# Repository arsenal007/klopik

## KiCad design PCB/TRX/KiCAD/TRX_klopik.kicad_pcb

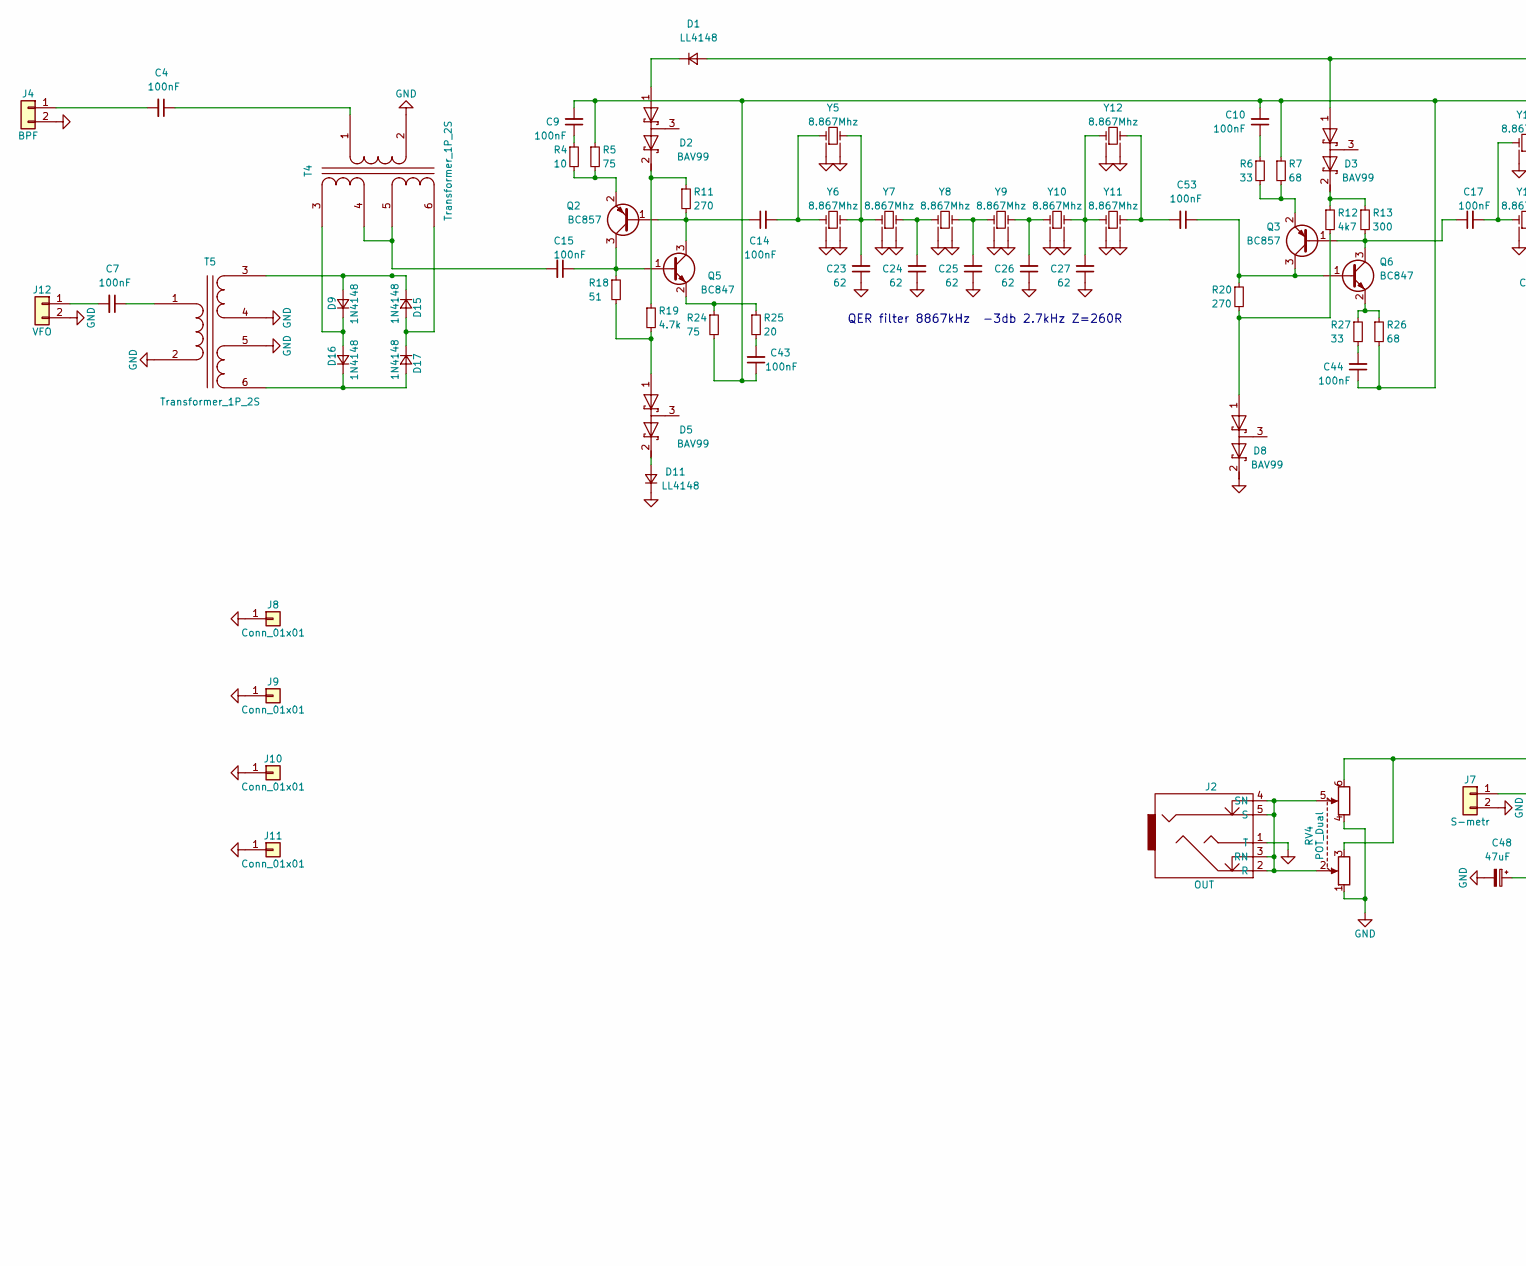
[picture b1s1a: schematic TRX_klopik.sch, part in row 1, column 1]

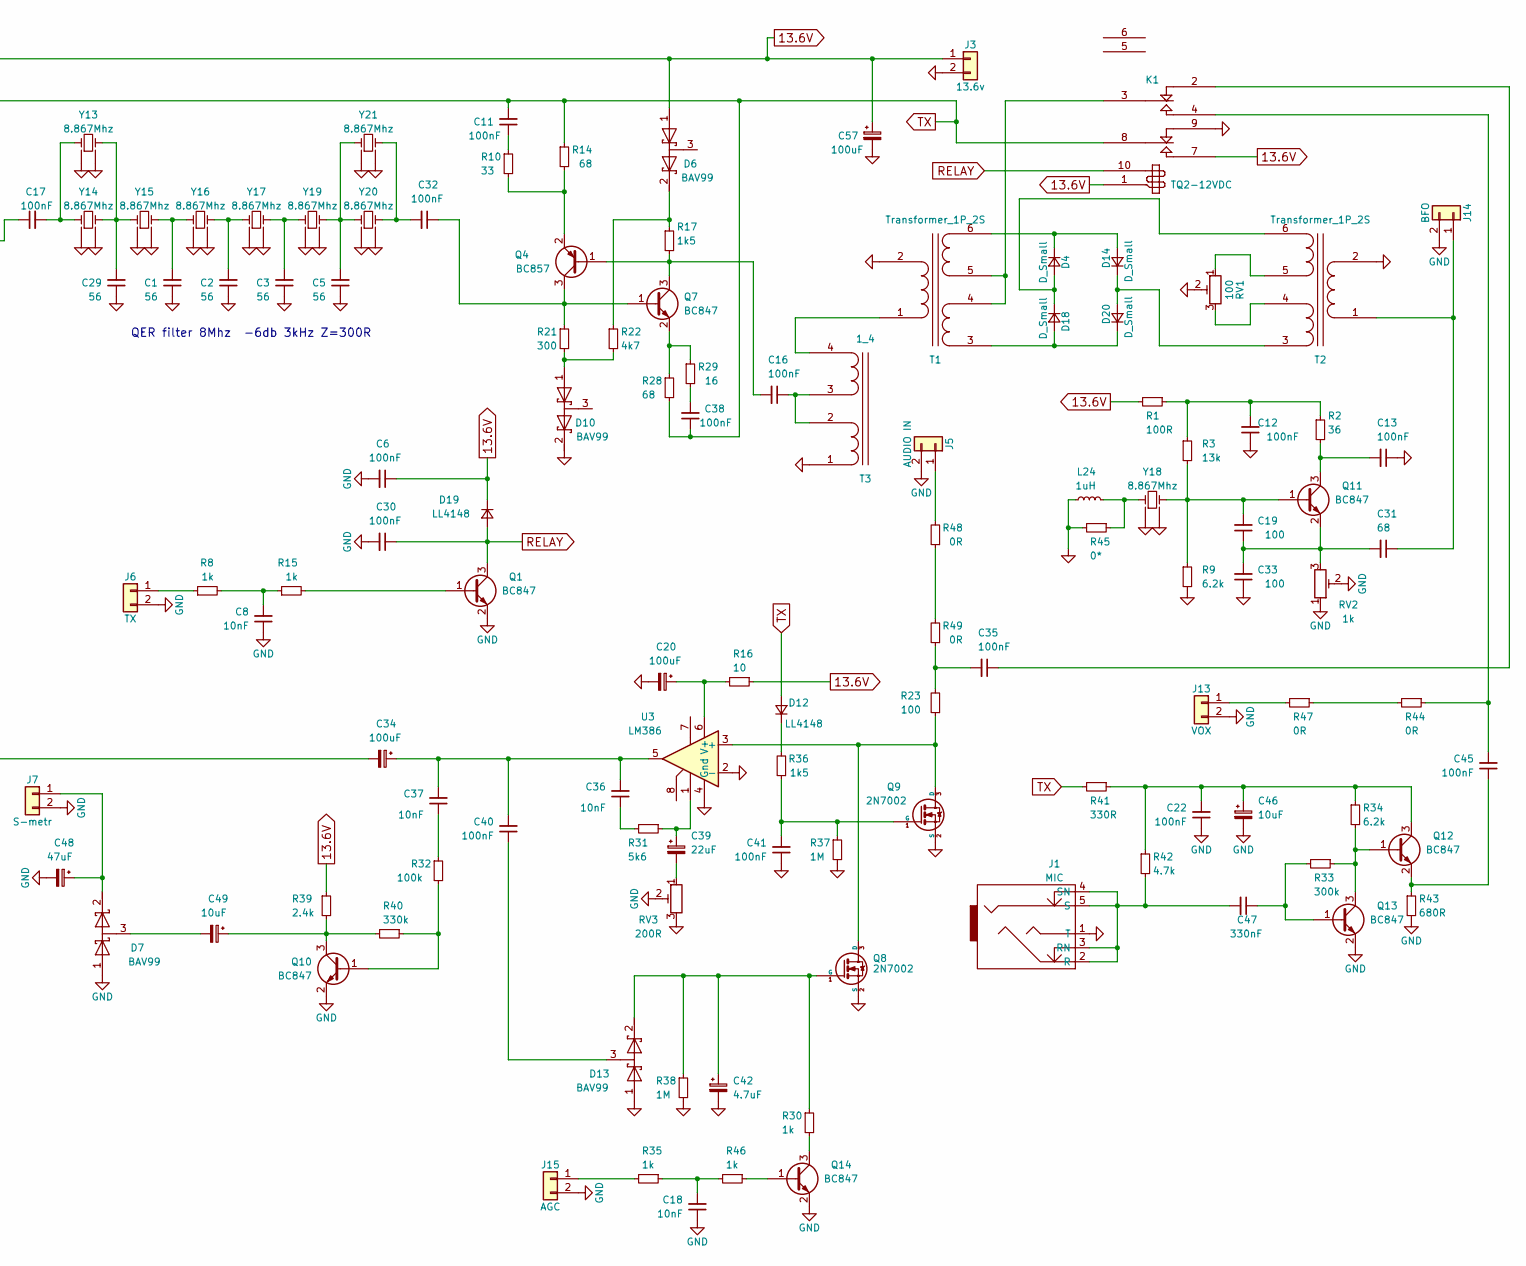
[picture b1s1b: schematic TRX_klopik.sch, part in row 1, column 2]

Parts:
C1, C2, C3, C5, C29: 56; C_1206_0603
C4, C6, C7, C9, C10, C11, C12, C13, C14, C15, C16, C17, C22, C30, C32, C35, C38, C40, C41, C43, C44, C45, C53: 100nF; C_1206_0603
C8, C18, C37: 10nF; C_0603_HandSoldering
C19, C33: 100; C_1206_0603
C20, C34, C57: 100uF; CP_Radial_D6.3mm_P2.50mm
C23, C24, C25, C26, C27: 62; C_1206_0603
C31: 68; C_1206_0603
C36: 10nF; C_1206_0603
C39: 22uF; CP_Tantalum_Case-A_EIA-3216-18_Hand
C42: 4.7uF; CP_Tantalum_Case-A_EIA-3216-18_Hand
C46, C49: 10uF; CP_Tantalum_Case-A_EIA-3216-18_Hand
C47: 330nF; C_1206_0603
C48: 47uF; CP_Radial_D6.3mm_P2.50mm
D1, D11, D12, D19: LL4148; D_MiniMELF_Handsoldering
D2, D3, D5, D6, D7, D8, D10, D13: BAV99; SOT-23_Handsoldering
D4, D14, D18, D20: D_Small; D_DO-35_SOD27_P7.62mm_Horizontal
D9, D15, D16, D17: 1N4148; D_DO-35_SOD27_P7.62mm_Horizontal
J1: MIC; audio_jack_3_5mm_PJ307
J2: OUT; audio_jack_3_5mm_PJ307
J3: 13.6v; Pin_Header_Straight_1x02_Pitch2.54mm
J4: BPF; RFCONNECTOR
J5: AUDIO IN; Pin_Header_Straight_1x02_Pitch2.54mm
J6: TX; Pin_Header_Straight_1x02_Pitch2.54mm
J7: S-metr; Pin_Header_Straight_1x02_Pitch2.54mm
J8, J9, J10, J11: Conn_01x01; MountingHole_3.2mm_M3_DIN965_Pad
J12: VFO; RFCONNECTOR
J13: VOX; Pin_Header_Straight_1x02_Pitch2.54mm
J14: BFO; Pin_Header_Straight_1x02_Pitch2.54mm
J15: AGC; Pin_Header_Straight_1x02_Pitch2.54mm
K1: TQ2-12VDC; Relay_DPDT_FRT5
L24: 1uH; Choke_Toroid_6,5x13mm_Vertical
Q1, Q5, Q6, Q7, Q10, Q11, Q12, Q13, Q14: BC847; SOT-23_Handsoldering
Q2, Q3, Q4: BC857; SOT-23_Handsoldering
Q8, Q9: 2N7002; SOT-23_Handsoldering
R1: 100R; R_1206_0603
R2: 36; R_1206_0603
R3: 13k; R_1206_0603
R4, R16: 10; R_1206_0603
R5, R24: 75; R_1206_0603
R6, R10, R27: 33; R_1206_0603
R7, R14, R26, R28: 68; R_1206_0603
R8, R15, R30, R35, R46: 1k; R_1206_0603
R9, R34: 6.2k; R_1206_0603
R11, R20: 270; R_1206_0603
R12, R22: 4k7; R_0603_HandSoldering
R13, R21: 300; R_1206_0603
R17: 1k5; R_1206_0603
R18: 51; R_1206_0603
R19: 4.7k; R_0603_HandSoldering
R23: 100; R_1206_0603
R25: 20; R_1206_0603
R29: 16; R_1206_0603
R31: 5k6; R_1206_0603
R32: 100k; R_1206_0603
R33: 300k; R_1206_0603
R36: 1k5; R_0805_HandSoldering
R37, R38: 1M; R_1206_0603
R39: 2.4k; R_1206_0603
R40: 330k; R_1206_0603
R41: 330R; R_1206_0603
R42: 4.7k; R_1206_0603
R43: 680R; R_1206_0603
R44, R47, R48, R49: 0R; R_1206_0603
R45: 0*; R_1206_0603
RV1: 100; Potentiometer_Trimmer_Piher_PT-6v_Horizontal
RV2: 1k; Potentiometer_Trimmer_Piher_PT-6v_Horizontal
RV3: 200R; Potentiometer_Trimmer_Piher_PT-6v_Horizontal
RV4: POT_Dual; Potentiometer_WH148_Double
T1, T2, T4, T5: Transformer_1P_2S; HF_transf3
T3: 1_4; TF14
U3: LM386; SOIC-8_3.9x4.9mm_Pitch1.27mm
Y5, Y6, Y7, Y8, Y9, Y10, Y11, Y12, Y13, Y14, Y15, Y16, Y17, Y18, Y19, Y20, Y21: 8.867Mhz; Crystal_HC49-U_Vertical

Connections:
13.6V: C6.1, C57.1, D1.2 (A), D3.1 (A), D6.1 (A), D19.1 (K), J3.1, K1.1 (+), K1.7 (T1), R1.2, R16.1, R39.1
GND: C1.1, C2.1, C3.1, C5.1, C6.2, C8.1, C12.1, C13.1, C18.1, C20.2, C22.1, C23.1, C24.1, C25.1, C26.1, C27.1, C29.1, C30.2, C33.1, C41.1, C42.2, C46.2, C48.2, C57.2, D7.1 (A), D8.2 (K), D10.2 (K), D11.1 (K), D13.1 (A), J1.1 (T), J2.1 (T), J3.2, J4.2, J5.2, J6.2, J7.2, J8.1, J9.1, J10.1, J11.1, J12.2, J13.2, J14.2, J15.2, K1.9 (R1), L24.1, Q1.2 (E), Q8.2 (S), Q9.2 (S), Q10.2 (E), Q13.2 (E), Q14.2 (E), R9.2, R37.2, R38.2, R43.2, R45.2, RV1.2, RV2.1, RV2.2, RV3.2, RV3.3, RV4.1, RV4.4, T1.2 (AB), T2.2 (AB), T3.1 (SA), T4.2 (AB), T5.2 (AB), T5.4 (SB), T5.5 (SC), U3.2 (-), U3.4 (Gnd), Y5.3 (GND), Y5.4 (GND), Y6.3 (GND), Y6.4 (GND), Y7.3 (GND), Y7.4 (GND), Y8.3 (GND), Y8.4 (GND), Y9.3 (GND), Y9.4 (GND), Y10.3 (GND), Y10.4 (GND), Y11.3 (GND), Y11.4 (GND), Y12.3 (GND), Y12.4 (GND), Y13.3 (GND), Y13.4 (GND), Y14.3 (GND), Y14.4 (GND), Y15.3 (GND), Y15.4 (GND), Y16.3 (GND), Y16.4 (GND), Y17.3 (GND), Y17.4 (GND), Y18.3 (GND), Y18.4 (GND), Y19.3 (GND), Y19.4 (GND), Y20.3 (GND), Y20.4 (GND), Y21.3 (GND), Y21.4 (GND)
unnamed: C1.2, Y15.2, Y16.1
unnamed: C2.2, Y16.2, Y17.1
unnamed: C3.2, Y17.2, Y19.1
unnamed: C4.1, T4.1 (AA)
unnamed: C4.2, J4.1
unnamed: C5.2, Y19.2, Y20.1, Y21.1
unnamed: C7.1, T5.1 (AA)
unnamed: C7.2, J12.1
unnamed: C8.2, R8.2, R15.1
unnamed: C9.1, R4.1
unnamed: C10.1, R6.1
unnamed: C11.1, R10.1
unnamed: C12.2, R1.1, R2.1, R3.1
unnamed: C13.2, Q11.3 (C), R2.2
unnamed: C14.1, Q2.1 (B), Q5.3 (C), R11.2
unnamed: C14.2, Y5.1, Y6.1
unnamed: C15.1, Q2.3 (C), Q5.1 (B), R18.1
unnamed: C15.2, T4.4 (SB), T4.5 (SC)
unnamed: C16.1, T3.2 (SB), T3.3 (SC)
unnamed: C16.2, Q4.1 (B), Q7.3 (C), R17.2
unnamed: C17.1, Q3.1 (B), Q6.3 (C), R13.2
unnamed: C17.2, Y13.1, Y14.1
unnamed: C18.2, R35.1, R46.2
unnamed: C19.1, C31.2, C33.2, Q11.2 (E), RV2.3
unnamed: C19.2, Q11.1 (B), R3.2, R9.1, Y18.2
unnamed: C20.1, R16.2, U3.6 (V+)
unnamed: C22.2, C46.1, Q12.3 (C), R34.1, R41.1, R42.1
unnamed: C23.2, Y5.2, Y6.2, Y7.1
unnamed: C24.2, Y7.2, Y8.1
unnamed: C25.2, Y8.2, Y9.1
unnamed: C26.2, Y9.2, Y10.1
unnamed: C27.2, Y10.2, Y11.1, Y12.1
unnamed: C29.2, Y13.2, Y14.2, Y15.1
unnamed: C31.1, J14.1, T2.1 (AA)
unnamed: C32.1, Q4.3 (C), Q7.1 (B), R21.1
unnamed: C32.2, Y20.2, Y21.2
unnamed: C34.1, C36.2, C37.2, C40.2, U3.5
unnamed: C34.2, RV4.3, RV4.6
unnamed: C35.1, K1.2 (R2)
unnamed: C35.2, R23.2, R49.1
unnamed: C36.1, R31.2
unnamed: C37.1, R32.1
unnamed: C38.2, R29.2
unnamed: C39.1, R31.1, U3.1
unnamed: C39.2, RV3.1
unnamed: C40.1, D13.3 (common)
unnamed: C41.2, Q9.1 (G), R36.1, R37.1
unnamed: C42.1, D13.2 (K), Q8.1 (G), R30.1, R38.1
unnamed: C43.2, R25.2
unnamed: C44.2, R27.2
unnamed: C45.1, Q12.2 (E), R43.1
unnamed: C45.2, K1.4 (T2), R44.1
unnamed: C47.1, Q13.1 (B), R33.2
unnamed: C47.2, J1.2 (R), J1.3 (RN), J1.4 (SN), J1.5 (S), R42.2
unnamed: C48.1, D7.2 (K), J7.1
unnamed: C49.1, Q10.3 (C), R39.2, R40.2
unnamed: C49.2, D7.3 (common)
unnamed: C53.1, Q3.3 (C), Q6.1 (B), R20.1
unnamed: C53.2, Y11.2, Y12.2
unnamed: D1.1 (K), D2.1 (A)
unnamed: D2.2 (K), R11.1, R19.1
unnamed: D3.2 (K), R12.1, R13.1
unnamed: D5.1 (A), R18.2, R19.2
unnamed: D6.2 (K), R17.1, R22.1
unnamed: D8.1 (A), R12.2, R20.2
unnamed: D10.1 (A), R21.2, R22.2
unnamed: D5.2 (K), D11.2 (A)
unnamed: D12.1 (K), R36.2
unnamed: D14.1 (K), D20.2 (A), T2.3 (SA)
unnamed: D4.1 (K), D14.2 (A), T1.6 (SD)
unnamed: D9.2 (A), D15.1 (K), T5.3 (SA)
unnamed: D15.2 (A), D17.1 (K), T4.6 (SD)
unnamed: D16.1 (K), D17.2 (A), T5.6 (SD)
unnamed: D9.1 (K), D16.2 (A), T4.3 (SA)
unnamed: D4.2 (A), D18.1 (K), T2.6 (SD)
unnamed: D18.2 (A), D20.1 (K), T1.3 (SA)
unnamed: J2.2 (R), J2.3 (RN), J2.4 (SN), J2.5 (S), RV4.2, RV4.5
unnamed: J5.1, R48.2
unnamed: J6.1, R8.1
unnamed: J13.1, R47.2
unnamed: J15.1, R35.2
unnamed: K1.3 (C2), T1.4 (SB), T1.5 (SC)
unnamed: L24.2, R45.1, Y18.1
unnamed: Q1.1 (B), R15.2
unnamed: Q2.2 (E), R4.2, R5.2
unnamed: Q3.2 (E), R6.2, R7.2
unnamed: Q4.2 (E), R10.2, R14.2
unnamed: Q5.2 (E), R24.1, R25.1
unnamed: Q6.2 (E), R26.1, R27.1
unnamed: Q7.2 (E), R28.1, R29.1
unnamed: Q8.3 (D), Q9.3 (D), R23.1, U3.3 (+)
unnamed: Q10.1 (B), R32.2, R40.1
unnamed: Q12.1 (B), Q13.3 (C), R33.1, R34.2
unnamed: Q14.1 (B), R46.1
unnamed: Q14.3 (C), R30.2
unnamed: R44.2, R47.1
unnamed: R48.1, R49.2
unnamed: RV1.1, T2.5 (SC)
unnamed: RV1.3, T2.4 (SB)
unnamed: T1.1 (AA), T3.4 (SD)
RELAY: C30.1, D19.2 (A), K1.10 (-), Q1.3 (C)
TX: C9.2, C10.2, C11.2, C38.1, C43.1, C44.1, D12.2 (A), K1.8 (C1), R5.1, R7.1, R14.1, R24.2, R26.2, R28.2, R41.2

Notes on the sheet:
QER filter 8867kHz -3db 2.7kHz Z=260R
QER filter 8Mhz -6db 3kHz Z=300R

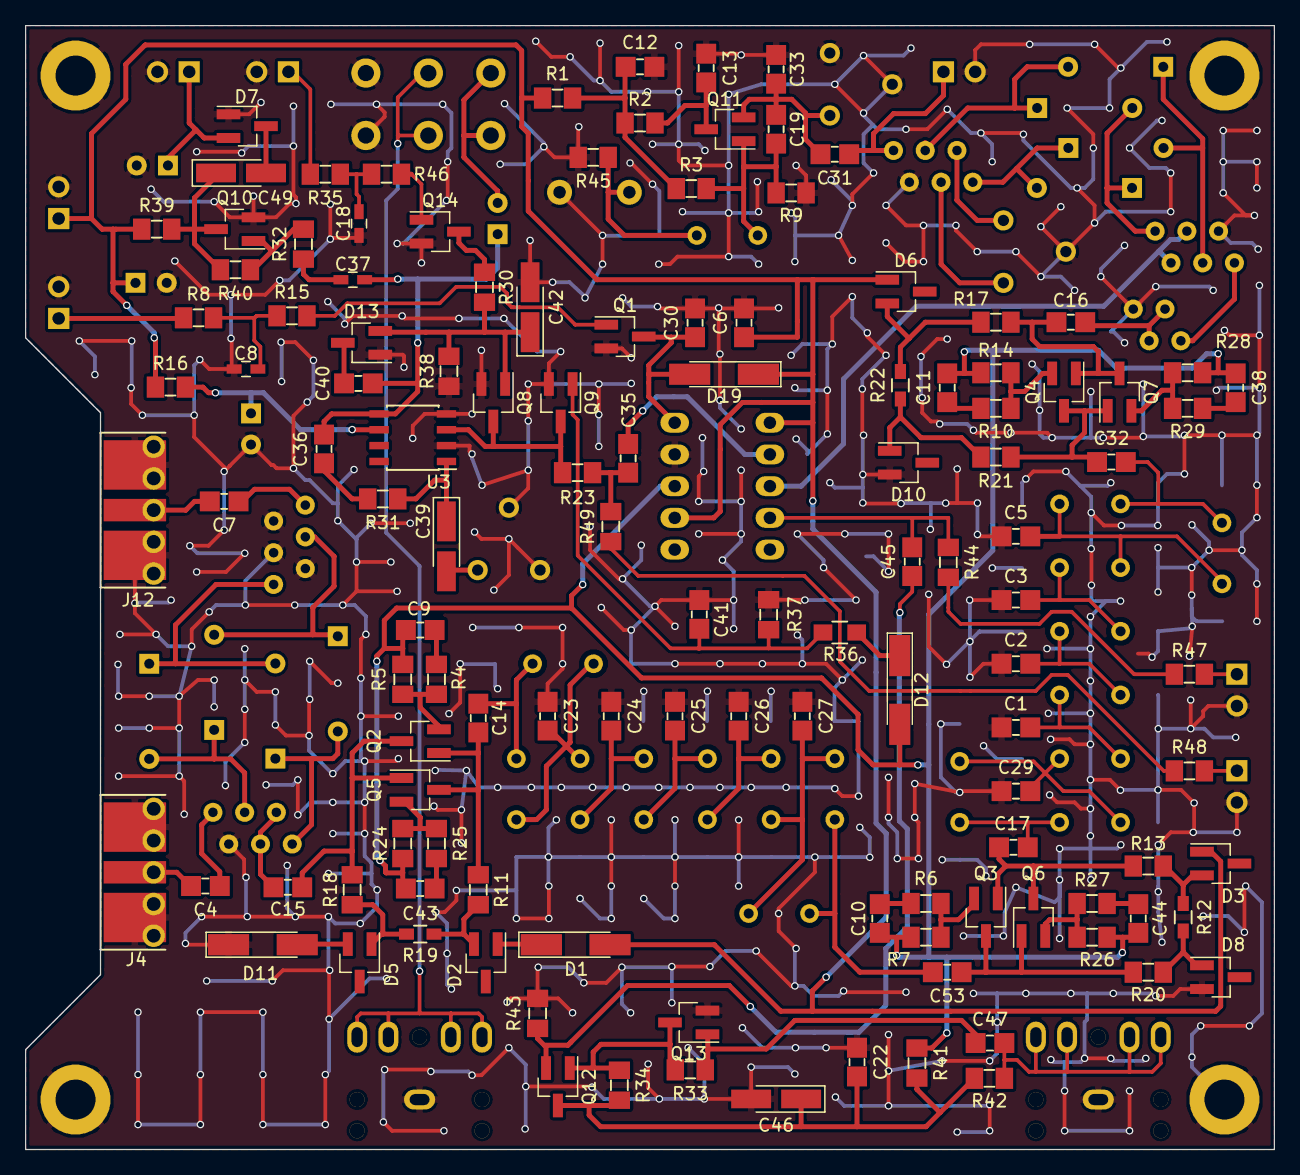
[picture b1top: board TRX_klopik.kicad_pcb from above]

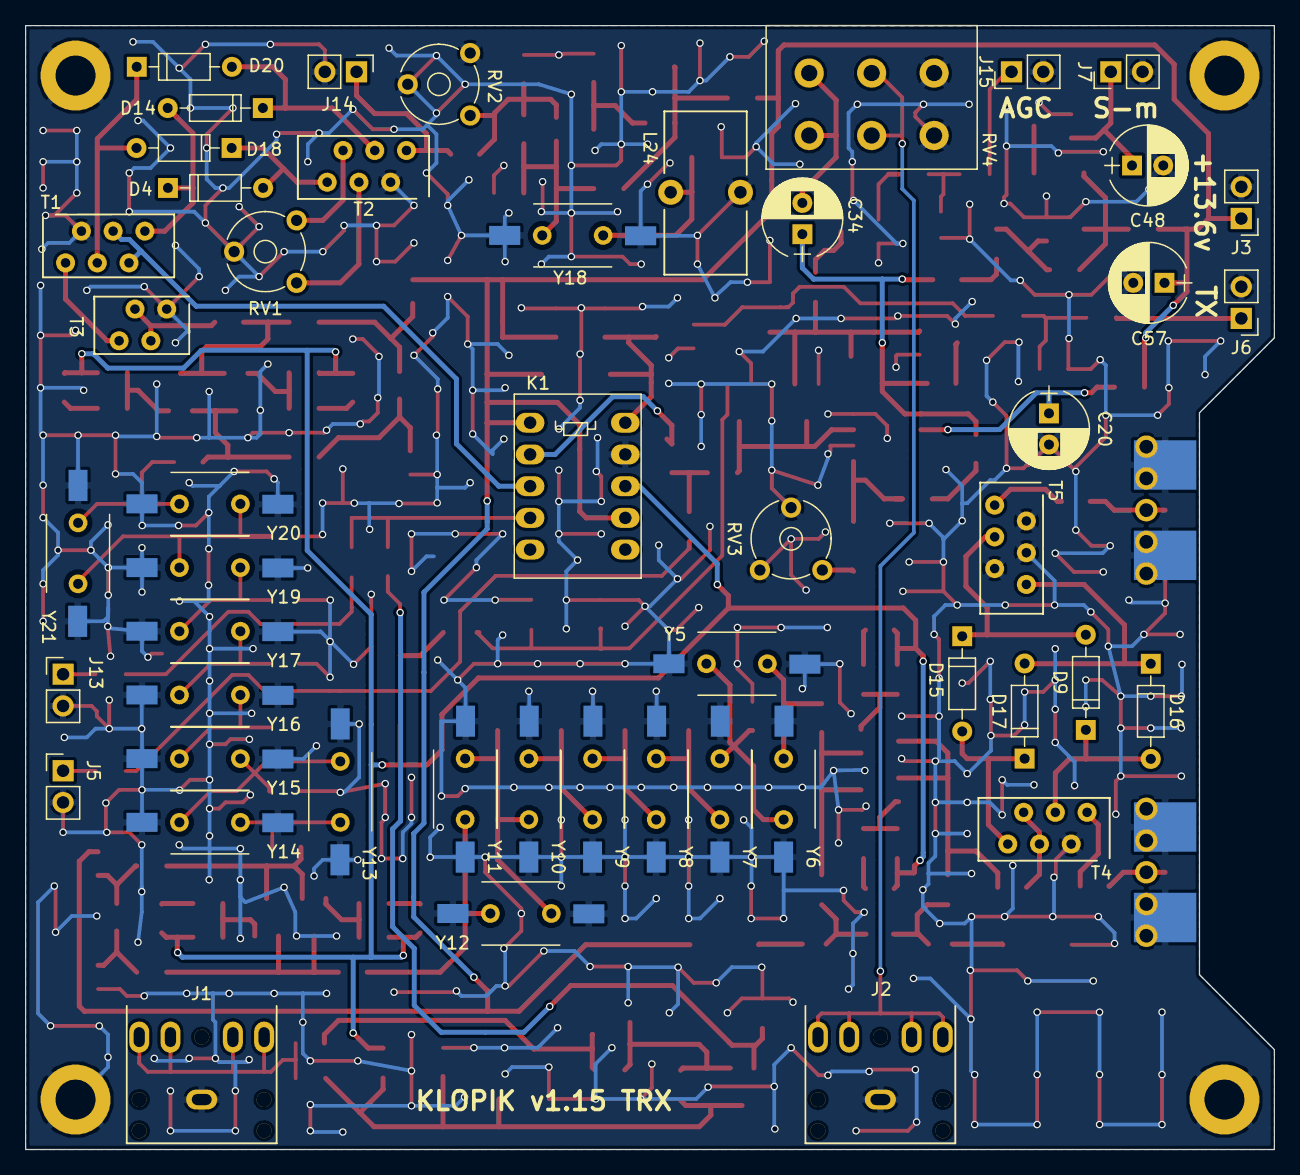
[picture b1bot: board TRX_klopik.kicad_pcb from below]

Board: 2 copper layers, 100.0 x 90.0 mm, 176 parts (51 on the bottom side), 104 nets.

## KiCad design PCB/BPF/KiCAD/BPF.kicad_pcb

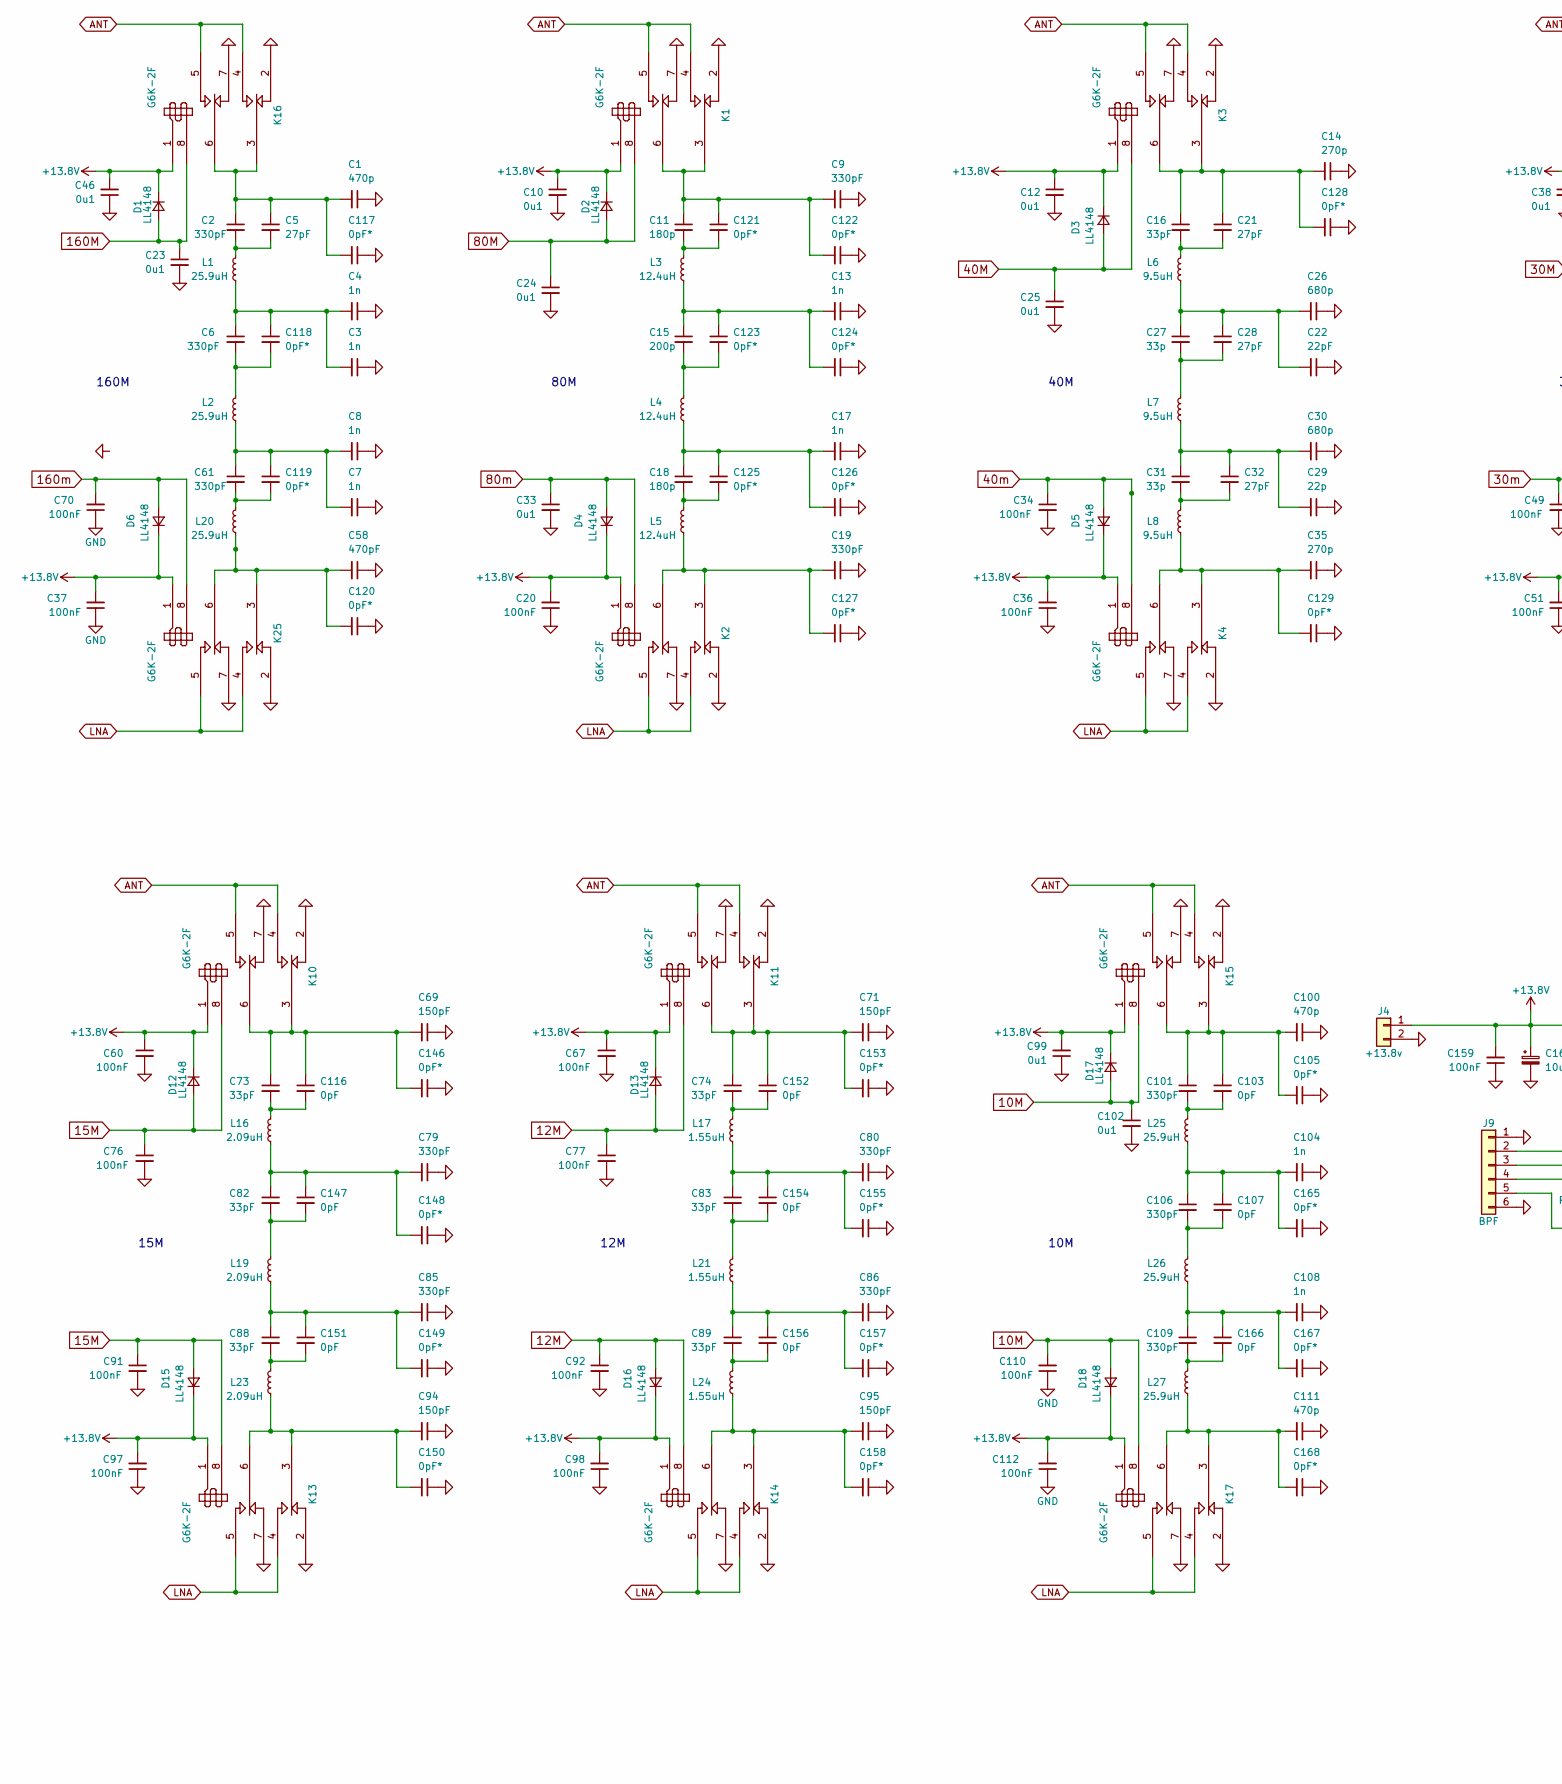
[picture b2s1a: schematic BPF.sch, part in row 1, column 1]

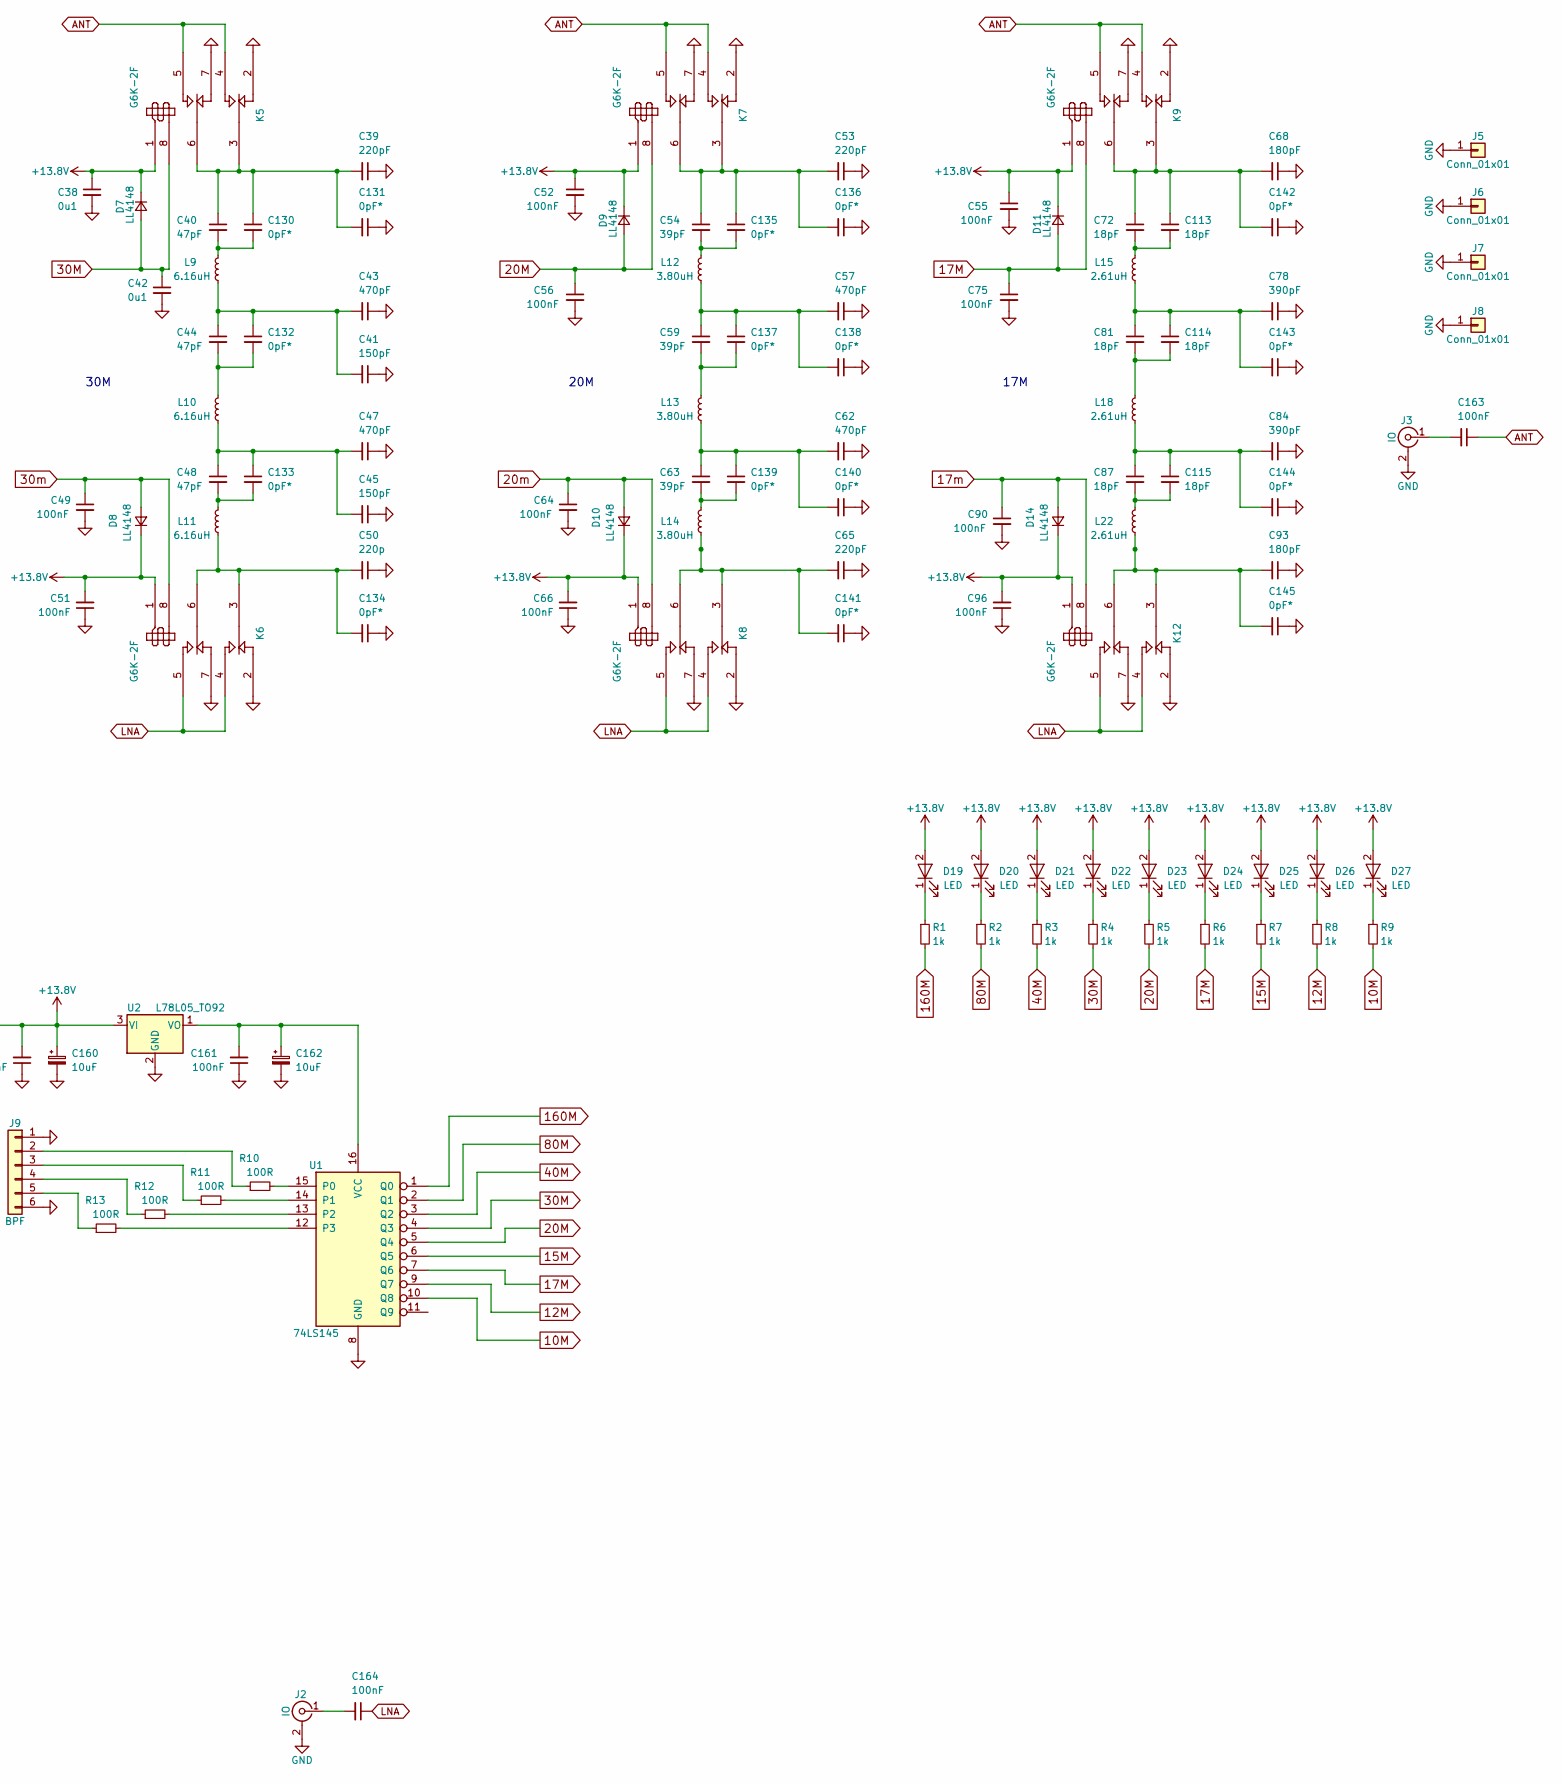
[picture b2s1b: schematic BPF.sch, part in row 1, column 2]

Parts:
C1, C100, C111: 470p; C_1206_0603
C2, C6, C9, C19, C61, C79, C80, C85, C86, C101, C106, C109: 330pF; C_1206_0603
C3, C4, C7, C8, C13, C17, C104, C108: 1n; C_1206_0603
C5, C21, C28, C32: 27pF; C_1206_0603
C10, C12, C23, C24, C25, C33, C38, C42, C46, C99, C102: 0u1; C_1206_0603
C11, C18: 180p; C_1206_0603
C14, C35: 270p; C_1206_0603
C15: 200p; C_1206_0603
C16, C73, C74, C82, C83, C88, C89: 33pF; C_1206_0603
C20, C34, C36, C37, C49, C51, C52, C55, C56, C60, C64, C66, C67, C70, C75, C76, C77, C90, C91, C92, C96, C97, C98, C110, C112, C159, C161, C163, C164: 100nF; C_1206_0603
C22: 22pF; C_1206_0603
C26, C30: 680p; C_1206_0603
C27, C31: 33p; C_1206_0603
C29: 22p; C_1206_0603
C39, C53, C65: 220pF; C_1206_0603
C40, C44, C48: 47pF; C_1206_0603
C41, C45, C69, C71, C94, C95: 150pF; C_1206_0603
C43, C47, C57, C58, C62: 470pF; C_1206_0603
C50: 220p; C_1206_0603
C54, C59, C63: 39pF; C_1206_0603
C68, C93: 180pF; C_1206_0603
C72, C81, C87, C113, C114, C115: 18pF; C_1206_0603
C78, C84: 390pF; C_1206_0603
C103, C107, C116, C147, C151, C152, C154, C156, C166: 0pF; C_1206_0603
C105, C117, C118, C119, C120, C121, C122, C123, C124, C125, C126, C127, C128, C129, C130, C131, C132, C133, C134, C135, C136, C137, C138, C139, C140, C141, C142, C143, C144, C145, C146, C148, C149, C150, C153, C155, C157, C158, C165, C167, C168: 0pF*; C_1206_0603
C160, C162: 10uF; CP_Tantalum_Case-A_EIA-3216-18_Hand
D1, D2, D3, D4, D5, D6, D7, D8, D9, D10, D11, D12, D13, D14, D15, D16, D17, D18: LL4148; D_MiniMELF_Handsoldering
D19, D20, D21, D22, D23, D24, D25, D26, D27: LED; LED_D3.0mm
J2, J3: IO; RFCONNECTOR
J4: +13.8v; Pin_Header_Straight_1x02_Pitch2.54mm
J5, J6, J7, J8: Conn_01x01; MountingHole_3.2mm_M3_DIN965_Pad
J9: BPF; Pin_Header_Straight_1x06_Pitch2.54mm
K1, K2, K3, K4, K5, K6, K7, K8, K9, K10, K11, K12, K13, K14, K15, K16, K17, K25: G6K-2F; Relay_G6K-2F
L1, L2, L20, L25, L26, L27: 25.9uH; Choke_Toroid_6,5x13mm_Vertical
L3, L4, L5: 12.4uH; Choke_Toroid_6,5x13mm_Vertical
L6, L7, L8: 9.5uH; Choke_Toroid_6,5x13mm_Vertical
L9, L10, L11: 6.16uH; Choke_Toroid_6,5x13mm_Vertical
L12, L13, L14: 3.80uH; Choke_Toroid_6,5x13mm_Vertical
L15, L18, L22: 2.61uH; Choke_Toroid_6,5x13mm_Vertical
L16, L19, L23: 2.09uH; Choke_Toroid_6,5x13mm_Vertical
L17, L21, L24: 1.55uH; Choke_Toroid_6,5x13mm_Vertical
R1, R2, R3, R4, R5, R6, R7, R8, R9: 1k; R_1206_0603
R10, R11, R12, R13: 100R; R_0603_HandSoldering
U1: 74LS145; SOIC-16_3.9x9.9mm_Pitch1.27mm
U2: L78L05_TO92; TO-92_Inline_Wide

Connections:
10M: C102.1, C110.2, D17.2 (A), D18.2 (A), K15.8 (-), K17.8 (-), R9.2, U1.10 (Q8)
12M: C77.1, C92.1, D13.2 (A), D16.2 (A), K11.8 (-), K14.8 (-), R8.2, U1.9 (Q7)
15M: C76.1, C91.1, D12.2 (A), D15.2 (A), K10.8 (-), K13.8 (-), R7.2, U1.6 (Q5)
17M: C75.1, C90.1, D11.2 (A), D14.2 (A), K9.8 (-), K12.8 (-), R6.2, U1.7 (Q6)
20M: C56.1, C64.1, D9.2 (A), D10.2 (A), K7.8 (-), K8.8 (-), R5.2, U1.5 (Q4)
30M: C42.1, C49.1, D7.2 (A), D8.2 (A), K5.8 (-), K6.8 (-), R4.2, U1.4 (Q3)
40M: C25.1, C34.1, D3.2 (A), D5.2 (A), K3.8 (-), K4.8 (-), R3.2, U1.3 (Q2)
80M: C24.1, C33.1, D2.2 (A), D4.2 (A), K1.8 (-), K2.8 (-), R2.2, U1.2 (Q1)
160M: C23.1, C70.2, D1.2 (A), D6.2 (A), K16.8 (-), K25.8 (-), R1.2, U1.1 (Q0)
+13.8V: C10.1, C12.1, C20.2, C36.2, C37.2, C38.1, C46.2, C51.2, C52.1, C55.1, C60.1, C66.2, C67.1, C96.2, C97.2, C98.2, C99.2, C112.2, C159.2, C160.1, D1.1 (K), D2.1 (K), D3.1 (K), D4.1 (K), D5.1 (K), D6.1 (K), D7.1 (K), D8.1 (K), D9.1 (K), D10.1 (K), D11.1 (K), D12.1 (K), D13.1 (K), D14.1 (K), D15.1 (K), D16.1 (K), D17.1 (K), D18.1 (K), D19.2 (A), D20.2 (A), D21.2 (A), D22.2 (A), D23.2 (A), D24.2 (A), D25.2 (A), D26.2 (A), D27.2 (A), J4.1, K1.1 (+), K2.1 (+), K3.1 (+), K4.1 (+), K5.1 (+), K6.1 (+), K7.1 (+), K8.1 (+), K9.1 (+), K10.1 (+), K11.1 (+), K12.1 (+), K13.1 (+), K14.1 (+), K15.1 (+), K16.1 (+), K17.1 (+), K25.1 (+), U2.3 (VI)
ANT: C163.1, K1.4 (T2), K1.5 (T1), K3.4 (T2), K3.5 (T1), K5.4 (T2), K5.5 (T1), K7.4 (T2), K7.5 (T1), K9.4 (T2), K9.5 (T1), K10.4 (T2), K10.5 (T1), K11.4 (T2), K11.5 (T1), K15.4 (T2), K15.5 (T1), K16.4 (T2), K16.5 (T1)
GND: C1.1, C3.1, C4.1, C7.1, C8.1, C9.1, C10.2, C12.2, C13.1, C14.1, C17.1, C19.1, C20.1, C22.1, C23.2, C24.2, C25.2, C26.1, C29.1, C30.1, C33.2, C34.2, C35.1, C36.1, C37.1, C38.2, C39.1, C41.1, C42.2, C43.1, C45.1, C46.1, C47.1, C49.2, C50.1, C51.1, C52.2, C53.1, C55.2, C56.2, C57.1, C58.1, C60.2, C62.1, C64.2, C65.1, C66.1, C67.2, C68.1, C69.1, C70.1, C71.1, C75.2, C76.2, C77.2, C78.1, C79.1, C80.1, C84.1, C85.1, C86.1, C90.2, C91.2, C92.2, C93.1, C94.1, C95.1, C96.1, C97.1, C98.1, C99.1, C100.1, C102.2, C104.1, C105.1, C108.1, C110.1, C111.1, C112.1, C117.1, C120.1, C122.1, C124.1, C126.1, C127.1, C128.1, C129.1, C131.1, C134.1, C136.1, C138.1, C140.1, C141.1, C142.1, C143.1, C144.1, C145.1, C146.1, C148.1, C149.1, C150.1, C153.1, C155.1, C157.1, C158.1, C159.1, C160.2, C161.1, C162.2, C165.1, C167.1, C168.1, J2.2 (Ext), J3.2 (Ext), J4.2, J5.1, J6.1, J7.1, J8.1, J9.1, J9.6, K1.2 (R2), K1.7, K2.2 (R2), K2.7, K3.2 (R2), K3.7, K4.2 (R2), K4.7, K5.2 (R2), K5.7, K6.2 (R2), K6.7, K7.2 (R2), K7.7, K8.2 (R2), K8.7, K9.2 (R2), K9.7, K10.2 (R2), K10.7, K11.2 (R2), K11.7, K12.2 (R2), K12.7, K13.2 (R2), K13.7, K14.2 (R2), K14.7, K15.2 (R2), K15.7, K16.2 (R2), K16.7, K17.2 (R2), K17.7, K25.2 (R2), K25.7, U1.8 (GND), U2.2 (GND)
LNA: C164.1, K2.4 (T2), K2.5 (T1), K4.4 (T2), K4.5 (T1), K6.4 (T2), K6.5 (T1), K8.4 (T2), K8.5 (T1), K12.4 (T2), K12.5 (T1), K13.4 (T2), K13.5 (T1), K14.4 (T2), K14.5 (T1), K17.4 (T2), K17.5 (T1), K25.4 (T2), K25.5 (T1)
unnamed: C1.2, C2.1, C5.1, C117.2, K16.3 (C2), K16.6
unnamed: C2.2, C5.2, L1.2
unnamed: C9.2, C11.1, C121.1, C122.2, K1.3 (C2), K1.6
unnamed: C11.2, C121.2, L3.2
unnamed: C16.2, C21.2, L6.2
unnamed: C22.2, C26.2, C27.1, C28.1, L6.1
unnamed: C27.2, C28.2, L7.2
unnamed: C29.2, C30.2, C31.1, C32.1, L7.1
unnamed: C31.2, C32.2, L8.2
unnamed: C100.2, C101.1, C103.1, C105.2, K15.3 (C2), K15.6
unnamed: C101.2, C103.2, L25.2
unnamed: C104.2, C106.1, C107.1, C165.2, L25.1
unnamed: C106.2, C107.2, L26.2
unnamed: C108.2, C109.1, C166.1, C167.2, L26.1
unnamed: C109.2, C166.2, L27.2
unnamed: C111.2, C168.2, K17.3 (C2), K17.6, L27.1
unnamed: C68.2, C72.1, C113.1, C142.2, K9.3 (C2), K9.6
unnamed: C72.2, C113.2, L15.2
unnamed: C78.2, C81.1, C114.1, C143.2, L15.1
unnamed: C81.2, C114.2, L18.2
unnamed: C84.2, C87.1, C115.1, C144.2, L18.1
unnamed: C87.2, C115.2, L22.2
unnamed: C69.2, C73.1, C116.1, C146.2, K10.3 (C2), K10.6
unnamed: C73.2, C116.2, L16.2
unnamed: C3.2, C4.2, C6.1, C118.1, L1.1
unnamed: C6.2, C118.2, L2.2
unnamed: C7.2, C8.2, C61.1, C119.1, L2.1
unnamed: C61.2, C119.2, L20.2
unnamed: C58.2, C120.2, K25.3 (C2), K25.6, L20.1
unnamed: C13.2, C15.1, C123.1, C124.2, L3.1
unnamed: C15.2, C123.2, L4.2
unnamed: C17.2, C18.1, C125.1, C126.2, L4.1
unnamed: C18.2, C125.2, L5.2
unnamed: C19.2, C127.2, K2.3 (C2), K2.6, L5.1
unnamed: C14.2, C16.1, C21.1, C128.2, K3.3 (C2), K3.6
unnamed: C35.2, C129.2, K4.3 (C2), K4.6, L8.1
unnamed: C39.2, C40.1, C130.1, C131.2, K5.3 (C2), K5.6
unnamed: C40.2, C130.2, L9.2
unnamed: C41.2, C43.2, C44.1, C132.1, L9.1
unnamed: C44.2, C132.2, L10.2
unnamed: C45.2, C47.2, C48.1, C133.1, L10.1
unnamed: C48.2, C133.2, L11.2
unnamed: C50.2, C134.2, K6.3 (C2), K6.6, L11.1
unnamed: C53.2, C54.1, C135.1, C136.2, K7.3 (C2), K7.6
unnamed: C54.2, C135.2, L12.2
unnamed: C57.2, C59.1, C137.1, C138.2, L12.1
unnamed: C59.2, C137.2, L13.2
unnamed: C62.2, C63.1, C139.1, C140.2, L13.1
unnamed: C63.2, C139.2, L14.2
unnamed: C65.2, C141.2, K8.3 (C2), K8.6, L14.1
unnamed: C93.2, C145.2, K12.3 (C2), K12.6, L22.1
unnamed: C79.2, C82.1, C147.1, C148.2, L16.1
unnamed: C82.2, C147.2, L19.2
unnamed: C85.2, C88.1, C149.2, C151.1, L19.1
unnamed: C94.2, C150.2, K13.3 (C2), K13.6, L23.1
unnamed: C88.2, C151.2, L23.2
unnamed: C71.2, C74.1, C152.1, C153.2, K11.3 (C2), K11.6
unnamed: C74.2, C152.2, L17.2
unnamed: C80.2, C83.1, C154.1, C155.2, L17.1
unnamed: C83.2, C154.2, L21.2
unnamed: C86.2, C89.1, C156.1, C157.2, L21.1
unnamed: C89.2, C156.2, L24.2
unnamed: C95.2, C158.2, K14.3 (C2), K14.6, L24.1
unnamed: C161.2, C162.1, U1.16 (VCC), U2.1 (VO)
unnamed: C163.2, J3.1 (In)
unnamed: C164.2, J2.1 (In)
unnamed: D19.1 (K), R1.1
unnamed: D20.1 (K), R2.1
unnamed: D21.1 (K), R3.1
unnamed: D22.1 (K), R4.1
unnamed: D23.1 (K), R5.1
unnamed: D24.1 (K), R6.1
unnamed: D25.1 (K), R7.1
unnamed: D26.1 (K), R8.1
unnamed: D27.1 (K), R9.1
unnamed: J9.2, R10.1
unnamed: J9.3, R11.1
unnamed: J9.4, R12.1
unnamed: J9.5, R13.1
unnamed: R10.2, U1.15 (P0)
unnamed: R11.2, U1.14 (P1)
unnamed: R12.2, U1.13 (P2)
unnamed: R13.2, U1.12 (P3)

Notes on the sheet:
160M
80M
40M
30M
20M
17M
15M
12M
10M
